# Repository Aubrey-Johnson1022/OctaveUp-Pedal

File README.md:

April 6, 2026

Hello! My name is Aubrey Johnson, and I am a college student studying electrical engineering.
I started building guitar pedals to help deepen my understanding of my courses (I'm going through Circuits II right now,
so working with this circuit was very helpful). 

This is a heavily distorted Octave Up pedal, meaning that you will hear the note that your guitar is playing doubled and 
up one octave. 

Everything you need to construct this pedal yourself should be included in the files. The only things I am NOT going to include
in this repository are the drilling hole sizes for the pedal enclosure. You should find the following items throughout the 
repository:

-LTSPICE simulation of the circuit

-KiCad files of both the schematic and the PCB

-Source files so you can see where I found the circuit design

-List of components/parts necessary for the project

-Wiring schematic(s) for the peripherals (3PDT switch, potentiometer, power supply port, etc.)

This is only my second time building a pedal, so my PCB design is rather amateur-looking.
Please feel free to tweak any of these files to your liking.

Additionally, if any of the listed items are missing from the repository, they will be added as soon as the pedal is complete
(This project is still a work-in-progress as of the time of writing).

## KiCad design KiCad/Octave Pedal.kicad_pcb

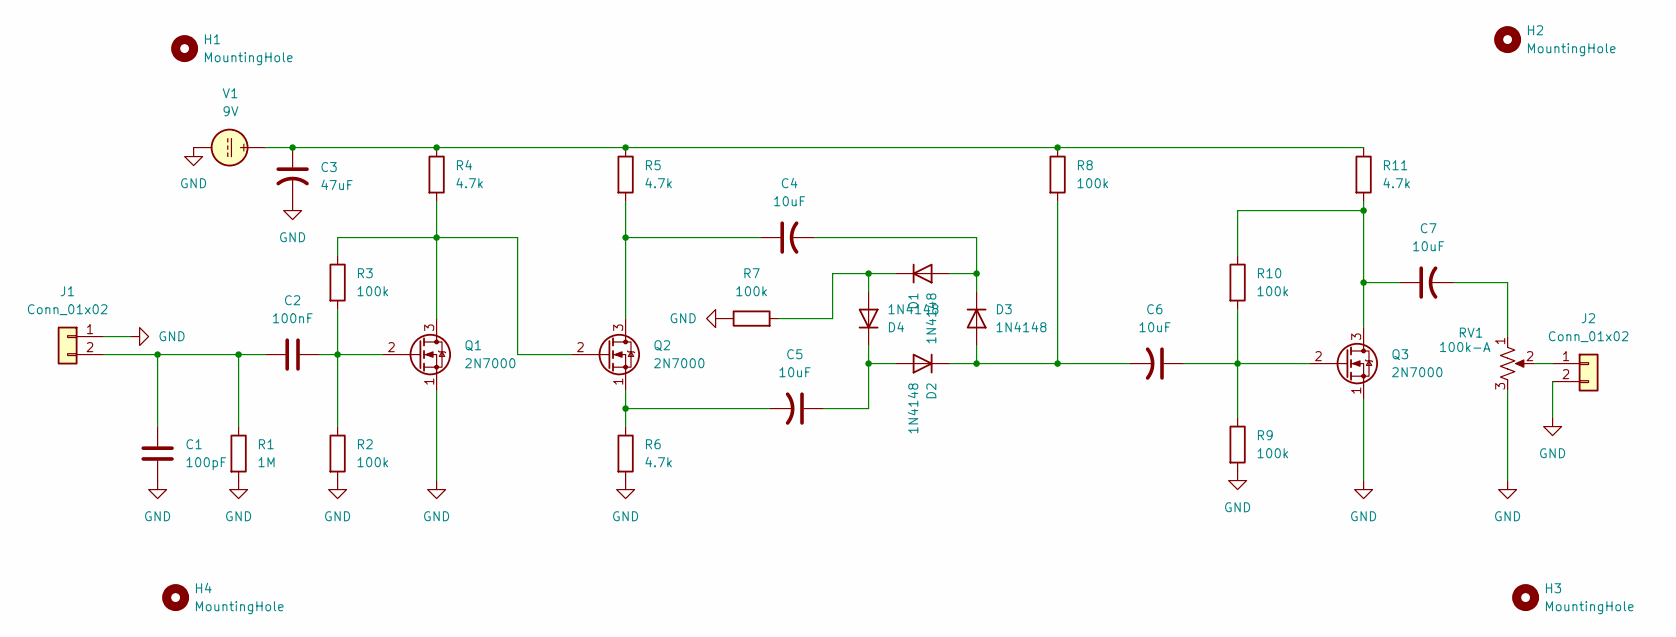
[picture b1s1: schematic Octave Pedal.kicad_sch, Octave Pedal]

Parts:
C1: 100pF; Capacitor_100pF_Radial
C2: 100nF; C_0603_1608Metric_Pad1.08x0.95mm_HandSolder
C3: 47uF; CP_Radial_D6.3mm_P2.50mm
C4, C5, C6, C7: 10uF; C_1206_3216Metric_Pad1.33x1.80mm_HandSolder
D1, D2, D3, D4: 1N4148; D_DO-35_SOD27_P7.62mm_Horizontal
H1, H2, H3, H4: MountingHole; MountingHole_3.2mm_M3
J1, J2: Conn_01x02; PinHeader_1x02_P2.54mm_Vertical
Q1, Q2, Q3: 2N7000; TO-92_Inline
R1: 1M; R_0805_2012Metric_Pad1.20x1.40mm_HandSolder
R2, R3, R7, R8, R9, R10: 100k; R_Axial_DIN0207_L6.3mm_D2.5mm_P5.08mm_Vertical
R4, R5, R6, R11: 4.7k; R_Axial_DIN0207_L6.3mm_D2.5mm_P7.62mm_Horizontal
RV1: 100k-A; Potentiometer_Alps_RK163_Single_Horizontal
V1: 9V; PinHeader_1x02_P2.54mm_Vertical

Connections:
GND: C1.2, C3.2, J1.1, J2.2, Q1.1 (S), Q3.1 (S), R1.2, R2.2, R6.2, R7.1, R9.2, RV1.3, V1.2
unnamed: C3.1, R4.1, R5.1, R8.1, R11.1, V1.1
unnamed: C7.2, RV1.1
unnamed: C4.2, D1.2 (A), D3.1 (K)
unnamed: D1.1 (K), D4.2 (A), R7.2
unnamed: C5.1, D2.2 (A), D4.1 (K)
unnamed: C6.2, D2.1 (K), D3.2 (A), R8.2
unnamed: C1.1, C2.2, J1.2, R1.1
unnamed: J2.1, RV1.2
unnamed: Q1.3 (D), Q2.2 (G), R3.1, R4.2
unnamed: C2.1, Q1.2 (G), R2.1, R3.2
unnamed: C4.1, Q2.3 (D), R5.2
unnamed: C5.2, Q2.1 (S), R6.1
unnamed: C7.1, Q3.3 (D), R10.1, R11.2
unnamed: C6.1, Q3.2 (G), R9.1, R10.2

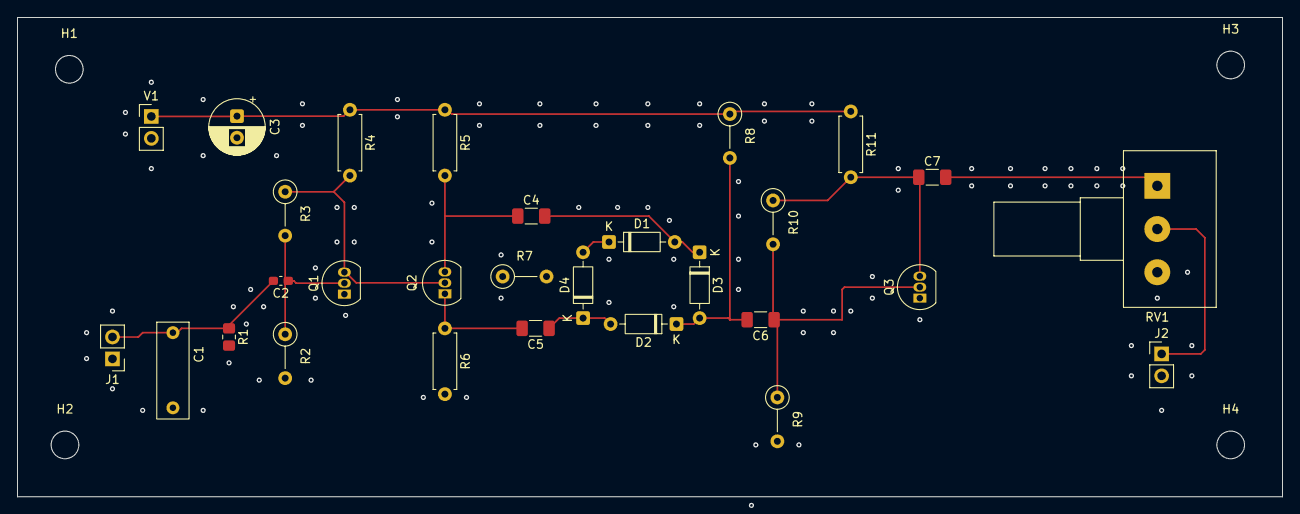
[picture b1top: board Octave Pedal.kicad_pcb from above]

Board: 2 copper layers, 146.5 x 55.5 mm, 33 parts (0 on the bottom side), 15 nets.

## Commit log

2026-04-06 KiCad Files
    These files contain both the circuit and PCB schematics for the octave pedal if you would like to tweak it in any way.
2026-04-06 Sources
    The original schematic I used to create my LTSPICE and KiCad schematics along with the link to the website where I found it.
2026-04-06 LTSPICE
    I am including my LTSPICE files for this circuit so that you can tinker with and adjust the circuit to get an output of your liking. As it stands, the circuit produces a heavily clipped waveform, whi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
2026-04-06 Rename Circuit Schematic.webp to Sources/Circuit Schematic.webp
2026-04-06 Rename Octave Pedal.asc to LTSPICE/Octave Pedal.asc
2026-04-06 Rename Octave Pedal.kicad_pcb to KiCad/Octave Pedal.kicad_pcb
2026-04-06 Rename Octave Pedal.kicad_pro to KiCad/Octave Pedal.kicad_pro
2026-04-06 Rename Octave Pedal.kicad_sch to KiCad/Octave Pedal.kicad_sch
2026-04-06 Rename Octave Pedal.log to LTSPICE/Octave Pedal.log
2026-04-06 Rename Octave Pedal.raw to LTSPICE/Octave Pedal.raw
2026-04-06 Rename Schematic Source Post.txt to Sources/Schematic Source Post.txt
